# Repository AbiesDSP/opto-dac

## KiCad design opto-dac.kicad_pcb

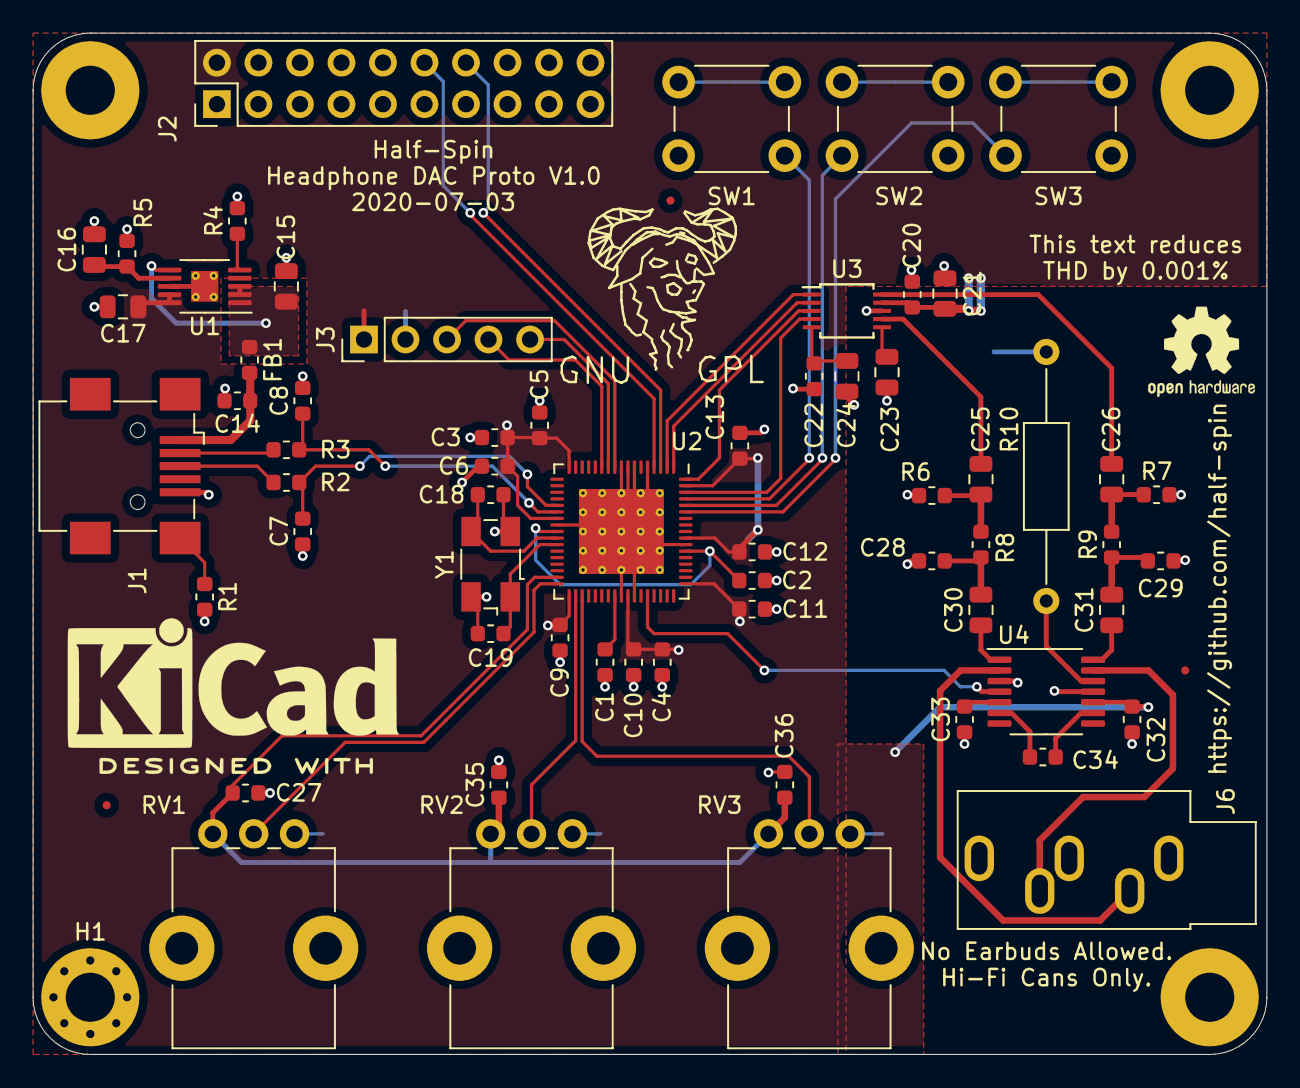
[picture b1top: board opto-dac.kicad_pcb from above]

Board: 2 copper layers, 75.5 x 62.5 mm, 69 parts (0 on the bottom side), 48 nets.

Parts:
C1, C2, C3, C4, C27, C32, C33, C34, C35, C36: 1uF; C_0603_1608Metric
C5, C6, C9, C10, C11, C12, C13, C14, C20, C22: 0.1uF; C_0603_1608Metric
C7, C8, C18, C19: 15pF; C_0603_1608Metric
C15, C16, C17, C21: 4.7uF; C_0805_2012Metric
C23: 10uF; C_0805_2012Metric
C24, C25, C26, C30, C31: 3.3uF; C_0805_2012Metric
C28, C29: 2.7nF; C_0603_1608Metric
FB1: L_0603_1608Metric
FID1, FID2, FID3: Fiducial_0.5mm_Mask1.5mm
H1: MountingHole_3mm_Pad_Via
H2, H3, H4: MountingHole_3mm_Pad
J1: USB_B_Mini; USB_Mini-B_Wuerth_65100516121_Horizontal
J2: Bluetooth; PinHeader_2x10_P2.54mm_Vertical
J3: Conn_01x05_Male; PinHeader_1x05_P2.54mm_Vertical
J6: Headphones; Jack_3.5mm_CUI_SJ1-3535NG_Horizontal
R1: R; R_0603_1608Metric
R2, R3: 27; R_0603_1608Metric
R4: 1k; R_0603_1608Metric
R5: 33.2k; R_0603_1608Metric
R6, R7: 10k; R_0603_1608Metric
R8, R9: 470; R_0603_1608Metric
R10: 82k; R_Axial_DIN0207_L6.3mm_D2.5mm_P15.24mm_Horizontal
RV1, RV2, RV3: 100k; Potentiometer_Bourns_PTV09A-1_Single_Vertical
SW1, SW2, SW3: SW_PUSH_6mm_H13mm
U1: LT3042xMSE; MSOP-10-1EP_3x3mm_P0.5mm_EP1.68x1.88mm_ThermalVias
U2: CY8C5888LTI-LP097; QFN-68-1EP_8x8mm_P0.4mm_EP5.2x5.2mm_ThermalVias
U3: CS4344; TSSOP-10_3x3mm_P0.5mm
U4: TPA6139A2; TSSOP-14_4.4x5mm_P0.65mm
Y1: 12.288MHz; Crystal_SMD_Abracon_ABM3B-4Pin_5.0x3.2mm

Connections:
+3V3: C3.1, C4.1, C5.1, C6.1, C9.1, C10.1, C11.1, C12.1, C13.1, C17.1, C20.1, C21.1, C32.2, J2.2, J3.1, U1.9, U1.10, U2.17, U2.24, U2.35, U2.44, U2.52, U2.59, U2.67, U3.9, U4.10
+5V: C15.1, FB1.1, U1.1, U1.2, U1.3, U1.6
/a0: RV1.2, U2.34
/a1: RV2.2, U2.36
/a2: RV3.2, U2.37
/as: C27.1, C35.1, C36.1, RV1.1, RV2.1, RV3.1, U2.33
/bt_rx: J2.12, U2.4
/bt_tx: J2.14, U2.3
/dac_l: C28.2, C30.2, R8.1
/dac_r: C29.1, C31.2, R9.1
/i2s_lrck: U2.68, U3.3
/i2s_mck: U2.66, U3.4
/i2s_sck: U2.1, U3.2
/i2s_sdo: U2.2, U3.1
/sw1: SW1.1, U2.65
/sw2: SW2.2, U2.64
/sw3: SW3.1, U2.63
/swdck: J3.4, U2.12
/swdio: J3.5, U2.11
/usb_d+: C7.2, R2.1, U2.22
/usb_d-: C8.1, R3.1, U2.23
/usb_vbus: C14.1, FB1.2, J1.1
/vcca: C1.1, U2.42
/vccd: C2.1, U2.26, U2.57
/xi: C19.1, U2.28, Y1.1
/xo: C18.1, U2.27, Y1.3
/xres: J3.3, U2.10
/~mute~: U2.47, U4.4
EPAD: C1.2, C2.2, C3.2, C4.2, C5.2, C6.2, C7.1, C8.2, C9.2, C10.2, C11.2, C12.2, C13.2, C14.2, C15.2, C16.2, C17.2, C18.2, C19.2, C20.2, C21.2, C22.2, C23.1, C24.2, C27.2, C28.1, C29.2, C32.1, C33.1, C35.2, C36.2, H1.1, J1.5, J2.1, J3.2, J6.S, R1.2, R4.2, R5.2, R6.1, R7.2, R10.2, RV1.3, RV2.3, RV3.3, SW1.2, SW2.1, SW3.2, U1.8, U1.11, U2.5, U2.7, U2.8, U2.9, U2.25, U2.43, U2.45, U2.58, U2.69, U3.8, U4.3, U4.11, Y1.2, Y1.4
unnamed: C16.1, R5.1, U1.7
unnamed: C22.1, C24.1, U3.5
unnamed: C23.2, U3.6
unnamed: C25.1, R6.2, R8.2
unnamed: C25.2, U3.7
unnamed: C26.1, R7.1, R9.2
unnamed: C26.2, U3.10
unnamed: C30.1, U4.1
unnamed: C31.1, U4.14
unnamed: C33.2, U4.5
unnamed: C34.1, U4.9
unnamed: C34.2, U4.6
unnamed: J1.2, R3.2
unnamed: J1.3, R2.2
unnamed: J1.6, R1.1
unnamed: J6.R, U4.13
unnamed: J6.T, U4.2
unnamed: R4.1, U1.5
unnamed: R10.1, U4.12

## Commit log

2020-11-15 Import project from headphone dac proto. Fix libraries, paths, gitignores.
